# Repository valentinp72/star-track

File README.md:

# star-track

Motorised alt-azimuth mount for a 114/900 Newtonian reflector (Omegon 114/900),
controlled from a phone, with a joystick, buttons and an emergency stop for manual use.

This branch restarts the project. It currently holds design notes, an interactive 3D
model of the mount, the electronics schematic and PCB, and a board test sketch; no mount
firmware yet.

## Contents

| Path | What it is |
| --- | --- |
| [`docs/architecture.md`](docs/architecture.md) | Planned electronics and software: ESP32-S3 controller, battery power, pins, phone web app, firmware structure, safety. |
| [`docs/mechanics.md`](docs/mechanics.md) | Current mechanical build (dimensions from the CAD model), bearing redesign, battery placement, base stability, transport. |
| [`docs/3d/index.html`](docs/3d/index.html) | Interactive 3D model of the redesigned mount. Open it in a browser (needs an internet connection to load three.js from a CDN). |
| [`electronics/`](electronics/) | KiCad schematic: power input and battery, ESP32-S3 board, two TMC2209 drivers, GPS, E-stop, LEDs, hand unit (joystick and buttons). [PDF](electronics/star-track.pdf) and PNG exports alongside. Two-layer PCB for the board on the mount (through-hole, plus four SMD parts for hand soldering), and a stripboard alternative (24 × 56 holes) with pictures of both sides. |
| [`firmware/board-test/`](firmware/board-test/) | Arduino sketch (arduino-cli) that checks the soldered board from a serial menu: LEDs, E-stop, GPS, motors, hand unit. |

## Earlier attempts

| Branch | Period | Approach |
| --- | --- | --- |
| `v1` | 2019–2020 | Single-board computer generating step pulses itself (wiringPi, C and Python), emergency button as a systemd service. |
| `v2` | 2023 | Orange Pi "brain" (Flask REST API + Skyfield) with an Ionic/Vue client packaged for iOS with Capacitor; planned Arduino "muscle" for the motors. |
| `v3` | 2025 | ESP-IDF Wi-Fi access point example on an ESP32 (previously `main`). |

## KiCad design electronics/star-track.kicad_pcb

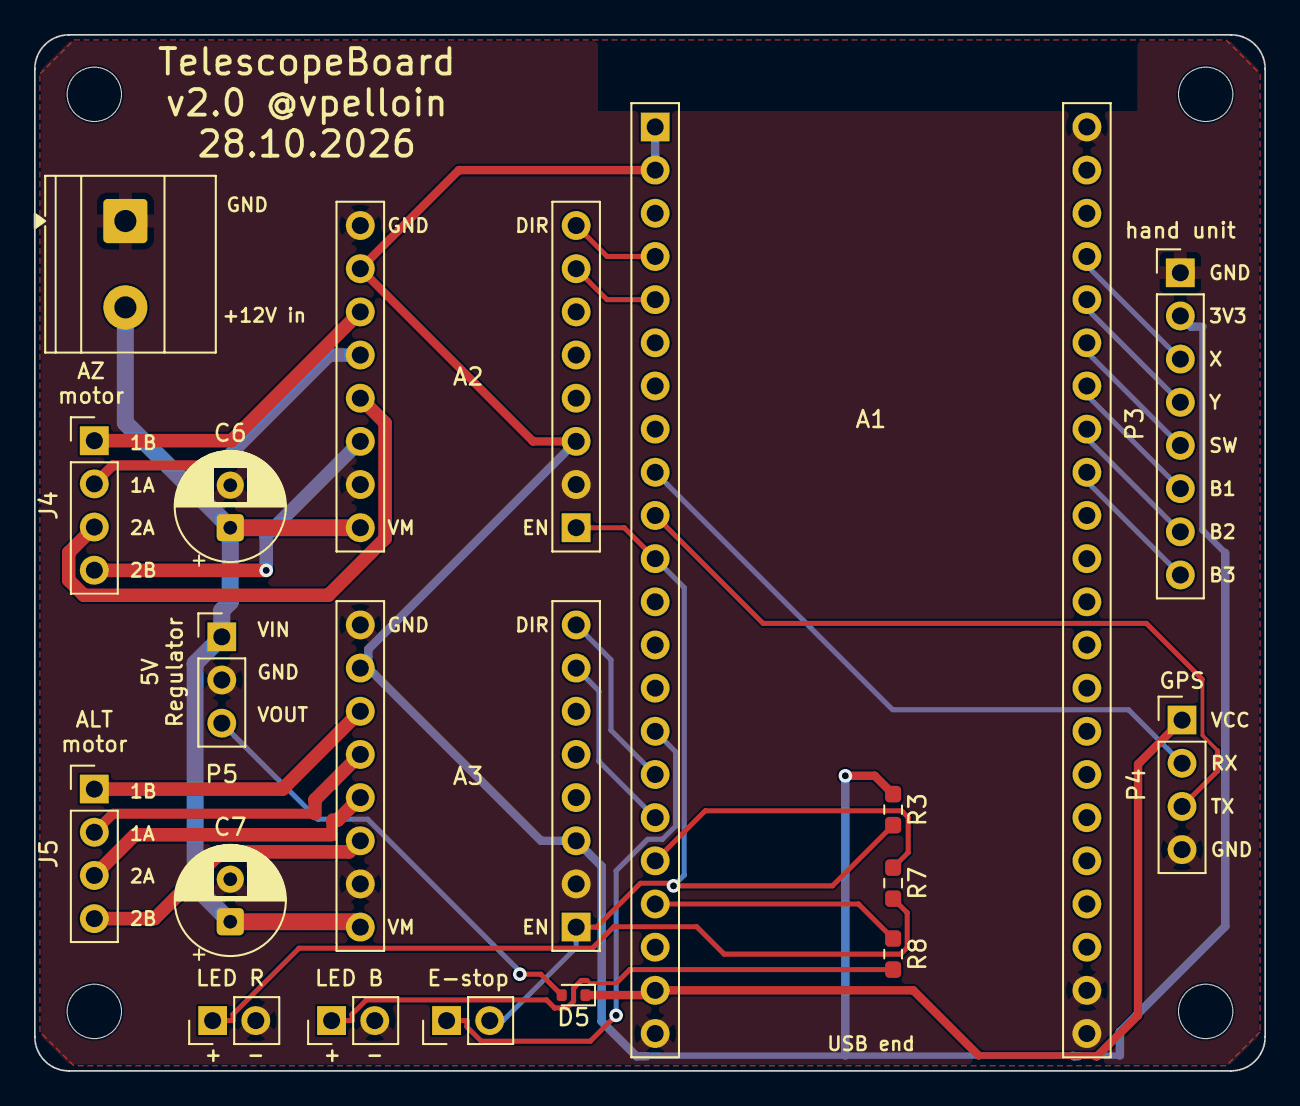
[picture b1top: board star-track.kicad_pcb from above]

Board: 2 copper layers, 72.4 x 61.0 mm, 22 parts (0 on the bottom side), 31 nets.

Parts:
A1: ESP32-S3-DevKitC-1; ESP32-S3-DevKitC-1_Socket
A2: TMC2209 AZ; TMC2209_StepStick_Socket
A3: TMC2209 ALT; TMC2209_StepStick_Socket
C6, C7: 100µF 25V; CP_Radial_D6.3mm_P2.50mm
D5: PMEG3005EB; D_SOD-523
H1, H2, H3, H4: MountingHole_3.2mm_M3
J4: AZ motor; PinHeader_1x04_P2.54mm_Vertical
J5: ALT motor; PinHeader_1x04_P2.54mm_Vertical
P1: EK508V-02P; TerminalBlock_Phoenix_MKDS-1,5-2-5.08_1x02_P5.08mm_Horizont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
P2: Red LED (D3); PinHeader_1x02_P2.54mm_Vertical
P3: Hand unit (J2); PinHeader_1x08_P2.54mm_Vertical
P4: GPS (U2); PinHeader_1x04_P2.54mm_Vertical
P5: DC-DC 5V (U1); PinHeader_1x03_P2.54mm_Vertical
P6: Blue LED (D4); PinHeader_1x02_P2.54mm_Vertical
P7: E-stop (SW2); PinHeader_1x02_P2.54mm_Vertical
R3: 220; R_0603_1608Metric_Pad0.98x0.95mm_HandSolder
R7: 1k; R_0603_1608Metric_Pad0.98x0.95mm_HandSolder
R8: 330; R_0603_1608Metric_Pad0.98x0.95mm_HandSolder

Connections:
+3V3: A1.1, A1.2, A2.3, A2.15, A3.3, A3.15, P3.2, R3.1
+5V: A1.21, D5.1, P4.1
+12V: A2.9, A3.9, C6.1, C7.1, P1.2, P5.1
/5V_DCDC: D5.2, P5.3
/ALT_DIR: A1.16, A3.8
/ALT_STEP: A1.17, A3.7
/AZ_DIR: A1.4, A2.8
/AZ_STEP: A1.5, A2.7
/BTN1: A1.29, P3.6
/BTN2: A1.30, P3.7
/BTN3: A1.31, P3.8
/DRV_EN: A1.11, A2.1, A3.1, P7.2, R3.2
/EN_OUT: A1.15, P7.1
/GPS_RX: A1.9, P4.2
/GPS_TX: A1.10, P4.3
/JOY_SW: A1.28, P3.5
/JOY_X: A1.26, P3.3
/JOY_Y: A1.27, P3.4
/LED_BLUE: A1.19, R8.1
/LED_RED: A1.18, R7.1
GND: A1.22, A1.23, A1.43, A1.44, A2.2, A2.10, A2.16, A3.2, A3.10, A3.16, C6.2, C7.2, P1.1, P2.2, P3.1, P4.4, P5.2, P6.2
unnamed: A2.13, J4.2
unnamed: A2.14, J4.1
unnamed: A2.12, J4.3
unnamed: A2.11, J4.4
unnamed: A3.13, J5.2
unnamed: A3.14, J5.1
unnamed: A3.12, J5.3
unnamed: A3.11, J5.4
unnamed: P2.1, R7.2
unnamed: P6.1, R8.2

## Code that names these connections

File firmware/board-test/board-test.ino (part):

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// Serial console at 115200 baud on the ESP32 board's UART port. Pins as in
// docs/architecture.md.

const int PIN_AZ_DIR = 4, PIN_AZ_STEP = 5;
const int PIN_ALT_DIR = 10, PIN_ALT_STEP = 11;
const int PIN_EN_OUT = 9;   // LOW = drivers on, through the E-stop
const int PIN_DRV_EN = 18;  // reads the drivers' EN line
const int PIN_LED_RED = 12, PIN_LED_BLUE = 13;
const int PIN_GPS_TX = 16, PIN_GPS_RX = 17;  // ESP32 side
const int PIN_SPARE = 14;  // unconnected: UART TX while the GPS test only listens
const int PIN_JOY_X = 1, PIN_JOY_Y = 2, PIN_JOY_SW = 42;
const int PIN_BTN[3] = {41, 40, 39};

const long STEPS_PER_REV = 200L * 64;  // 1/64 microsteps (MS1 GND, MS2 3.3 V)
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
// Drivers

void driversOff() { digitalWrite(PIN_EN_OUT, HIGH); }
void driversOn() { digitalWrite(PIN_EN_OUT, LOW); }

// Moves one axis by the given number of steps, with a short linear ramp.
void move(int stepPin, int dirPin, long steps) {
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Result testLeds() {
  Serial.println("\n--- LEDs ---");
  Serial.println("Red LED on for 2 s.");
  analogWrite(PIN_LED_RED, 255);
  delay(2000);
  analogWrite(PIN_LED_RED, 0);
  char red = ask("Did the red LED light?");

  Serial.println("Blue LED on for 2 s.");
  analogWrite(PIN_LED_BLUE, 255);
  delay(2000);
  analogWrite(PIN_LED_BLUE, 0);
  char blue = ask("Did the blue LED light?");

  Serial.println("Both LEDs fade up and down (PWM).");
  for (int rep = 0; rep < 2; rep++)
    for (int i = 0; i <= 510; i += 5) {
      int v = i <= 255 ? i : 510 - i;
      analogWrite(PIN_LED_RED, v);
      analogWrite(PIN_LED_BLUE, v);
      delay(8);
    }
  analogWrite(PIN_LED_RED, 0);
  analogWrite(PIN_LED_BLUE, 0);
  char fade = ask("Did both fade smoothly?");

  if (red == 'n' || blue == 'n')
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  bool ok = true;

  // EN_OUT released, internal pull-up off: R3 alone must pull DRV_EN high.
  pinMode(PIN_EN_OUT, INPUT);
  pinMode(PIN_DRV_EN, INPUT);
  delay(5);
  int released = digitalRead(PIN_DRV_EN);
  Serial.printf("  EN_OUT released -> DRV_EN %s (expected HIGH)\n", released ? "HIGH" : "LOW");
  if (!released) {
    // The ESP32's weak internal pulls (about 45 kΩ) tell an open R3 from a line held low.
    pinMode(PIN_DRV_EN, INPUT_PULLDOWN);
    delay(5);
    int withPulldown = digitalRead(PIN_DRV_EN);
    pinMode(PIN_DRV_EN, INPUT_PULLUP);
    delay(5);
    int withPullup = digitalRead(PIN_DRV_EN);
    Serial.printf("  With internal pull-down: %s, with internal pull-up: %s\n",
                  withPulldown ? "HIGH" : "LOW", withPullup ? "HIGH" : "LOW");
    if (!withPulldown && withPullup) {
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      ok = false;
    }
  }
  pinMode(PIN_DRV_EN, INPUT_PULLUP);

  pinMode(PIN_EN_OUT, OUTPUT);
  driversOff();
  delay(5);
  int high = digitalRead(PIN_DRV_EN);
  Serial.printf("  EN_OUT HIGH     -> DRV_EN %s (expected HIGH)\n", high ? "HIGH" : "LOW");
  if (!high) ok = false;

  driversOn();
  delay(5);
  int low = digitalRead(PIN_DRV_EN);
  driversOff();
  Serial.printf("  EN_OUT LOW      -> DRV_EN %s (expected LOW, E-stop released)\n",
                low ? "HIGH" : "LOW");
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  unsigned long start = millis();
  flushInput();
  while (millis() - start < 10000 && !Serial.available())
    if (digitalRead(PIN_DRV_EN)) { pressSeen = true; break; }
  if (pressSeen) {
    Serial.println("  Pressed: DRV_EN HIGH, drivers off.");
    start = millis();
    while (millis() - start < 10000 && !Serial.available())
      if (!digitalRead(PIN_DRV_EN)) { releaseSeen = true; break; }
    if (releaseSeen) Serial.println("  Released: DRV_EN LOW.");
  }
  driversOff();
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
Result testGps() {
  Serial.println("\n--- GPS (P4, 9600 baud) ---");
  NmeaScan r = listenGps(PIN_GPS_RX, 9600, 5000);
  Serial.printf("  %ld bytes, %ld valid sentences, %ld bad in 5 s\n", r.bytes, r.good, r.bad);

  if (r.good == 0) {
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    for (int swapped = 0; swapped < 2; swapped++)
      for (long baud : bauds) {
        if (!swapped && baud == 9600) continue;
        NmeaScan t = listenGps(swapped ? PIN_GPS_TX : PIN_GPS_RX, baud, 2500);
        Serial.printf("    %s, %6ld baud: %ld bytes, %ld valid\n",
                      swapped ? "swapped" : "normal ", baud, t.bytes, t.good);
        if (t.good > 0) {
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      // Raw levels with a weak pull-down: an idle UART output from the module holds
      // the line HIGH, a wire that reaches nothing reads LOW.
      Serial.println("  Line levels for 1 s, internal pull-down on:");
      for (int pin : {PIN_GPS_RX, PIN_GPS_TX}) {
        pinMode(pin, INPUT_PULLDOWN);
        delay(5);
        long highs = 0, edges = 0, samples = 0;
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        }
        pinMode(pin, INPUT);
        Serial.printf("    GPIO%d (P4 %s): HIGH %ld%% of the time, %ld edges\n", pin,
                      pin == PIN_GPS_RX ? "pin 3, TX" : "pin 2, RX",
                      highs * 100 / samples, edges);
      }
      Serial.println("  FAIL: nothing received. If P4 pin 3 reads LOW all the time, the "
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
  driversOn();
  delay(5);
  if (digitalRead(PIN_DRV_EN)) {
    driversOff();
    Serial.println("  FAIL: DRV_EN is HIGH, the E-stop is pressed or P7 is open.");
    return R_FAIL;
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  delay(200);

  struct Axis { const char *name; int step, dir; } axes[] = {
      {"Azimuth (J4)", PIN_AZ_STEP, PIN_AZ_DIR},
      {"Altitude (J5)", PIN_ALT_STEP, PIN_ALT_DIR},
  };
  bool fail = false, allSkipped = true;
  for (auto &a : axes) {
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  flushInput();
  while (!Serial.available()) {
    Serial.printf("  X %4d  Y %4d  SW %s  B1 %s  B2 %s  B3 %s\n",
                  analogRead(PIN_JOY_X), analogRead(PIN_JOY_Y),
                  digitalRead(PIN_JOY_SW) ? "up  " : "DOWN",
                  digitalRead(PIN_BTN[0]) ? "up  " : "DOWN",
                  digitalRead(PIN_BTN[1]) ? "up  " : "DOWN",
                  digitalRead(PIN_BTN[2]) ? "up  " : "DOWN");
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void testEstopLive() {
  Serial.println("\n--- E-stop live, drivers on, any key to stop ---");
  Serial.println("  Red LED: DRV_EN HIGH, drivers off. Blue LED: DRV_EN LOW, drivers on.");
  pinMode(PIN_EN_OUT, OUTPUT);
  driversOn();
  flushInput();
  int last = -1;
  unsigned long lastPrint = 0;
  while (!Serial.available()) {
    int mv = analogReadMilliVolts(PIN_DRV_EN);
    pinMode(PIN_DRV_EN, INPUT_PULLUP);  // analogRead detaches the digital input
    delayMicroseconds(50);
    int level = digitalRead(PIN_DRV_EN);
    analogWrite(PIN_LED_RED, level ? 255 : 0);
    analogWrite(PIN_LED_BLUE, level ? 0 : 40);
    if (level != last || millis() - lastPrint > 1000) {
      Serial.printf("  DRV_EN %s, %4d mV\n", level ? "HIGH" : "LOW ", mv);
      last = level;
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    delay(20);
  }
  driversOff();
  analogWrite(PIN_LED_RED, 0);
  analogWrite(PIN_LED_BLUE, 0);
  pinMode(PIN_DRV_EN, INPUT_PULLUP);
  flushInput();
}

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
void setup() {
  // Drivers off before anything else.
  pinMode(PIN_EN_OUT, OUTPUT);
  driversOff();
  // Strongest output: EN_OUT holds DRV_EN low against the pull-up (about 15 mA through 220 Ω).
  gpio_set_drive_capability((gpio_num_t)PIN_EN_OUT, GPIO_DRIVE_CAP_3);
  pinMode(PIN_DRV_EN, INPUT_PULLUP);  // backs up R3
  for (int p : {PIN_AZ_STEP, PIN_AZ_DIR, PIN_ALT_STEP, PIN_ALT_DIR}) {
    pinMode(p, OUTPUT);
    digitalWrite(p, LOW);
  }
  analogWrite(PIN_LED_RED, 0);
  analogWrite(PIN_LED_BLUE, 0);
  pinMode(PIN_JOY_SW, INPUT_PULLUP);
  for (int p : PIN_BTN) pinMode(p, INPUT_PULLUP);

  Serial.begin(115200);
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
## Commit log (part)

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2019-07-27 begining of logic
2019-07-30 before rework from thread to process
2019-07-31 target reverse working
2019-08-03 is it working?
2019-08-03 yeah it seems to work properly
2020-02-23 début essais motor.c
2020-02-28 motor and emergency
2020-02-28 motor and emergency now working ; systemctl config ; makefile
2020-02-28 project tree structure
2020-02-28 makefile clean
2023-03-04 brain and muscle separation
2023-03-05 gitignore added node
2023-03-05 client ui with Vue.js and ionicframework
2023-03-05 removed old subfolder mess
2023-03-05 vue with PWA
2023-03-07 server env and first version
2023-03-07 client test with geolocation
2023-03-07 flask server with background thread
2023-03-07 working flask server with background process instead of thread
2023-03-07 separated the backend into a different file
2023-03-11 backend and flask server can now fully communicate between each other
2023-03-11 file locking to prevent multiple backend ; main backend loop now in the backend object
2023-03-11 added planets and some other objects with pictures and descriptions
2023-03-11 new routes and backend: planets, tracking and toggle state
2023-03-11 added weather (temp and pressure) to adjust for atmospheric refraction
2023-03-11 cleaned auto-generated doc for Flask
2023-03-12 test for pwa debugging
2023-03-12 SSL certs and root CA, with documentation
2023-03-12 New icon and splashscreen, working on iOS
2023-03-12 cleaning SSL cert generation, added config for "ionic serve" to be in httpS
2023-03-12 tabs renamed ; card POC for objects
2023-03-25 ObjectCard component start
2023-03-25 added logos
2023-03-25 updated README with full setup guide
2023-03-26 objectcards rendered using API data from server
2023-03-26 link on objectcard POC
2023-03-27 object card and swipe issues (not fixed)
2023-03-31 updated ionic from v6 to v7
2023-03-31 added nginx
2023-04-04 hack to disable Safari iOS PWA swipe back
2023-04-08 trying things with capacitor for ios deployment
2023-04-08 xcode
2023-04-08 action to export iOS as ipa
2023-04-08 nother workflow
2023-04-08 edited workflow
2023-04-08 updated workflow
2023-04-08 added alstore.json
2023-04-08 clean up of the workflows
2023-04-09 updated all logos and splashscreens
2023-04-09 rework on icons
2023-04-09 fixed iOS logo
2023-04-09 enabled back manual workflow
2023-04-10 fixed api target URL, now configurable
2023-04-10 added configurable API path
2023-04-10 toast that appears to warn if API is down
2023-04-10 added ping command, fixed images with API
2023-04-10 iOS: removed landscape, added gps authorization
2023-04-10 added GPS settings page
2023-04-11 fixed issue in gpsSettings (ion-button)
2023-04-11 (seems to be) fixed iOS splashscreen
2023-04-23 added link to download SSL certificate from API
2023-04-23 added security page
2024-01-24 change of timeout
2025-12-14 start new empty version
2025-12-17 wifi AP esp32
